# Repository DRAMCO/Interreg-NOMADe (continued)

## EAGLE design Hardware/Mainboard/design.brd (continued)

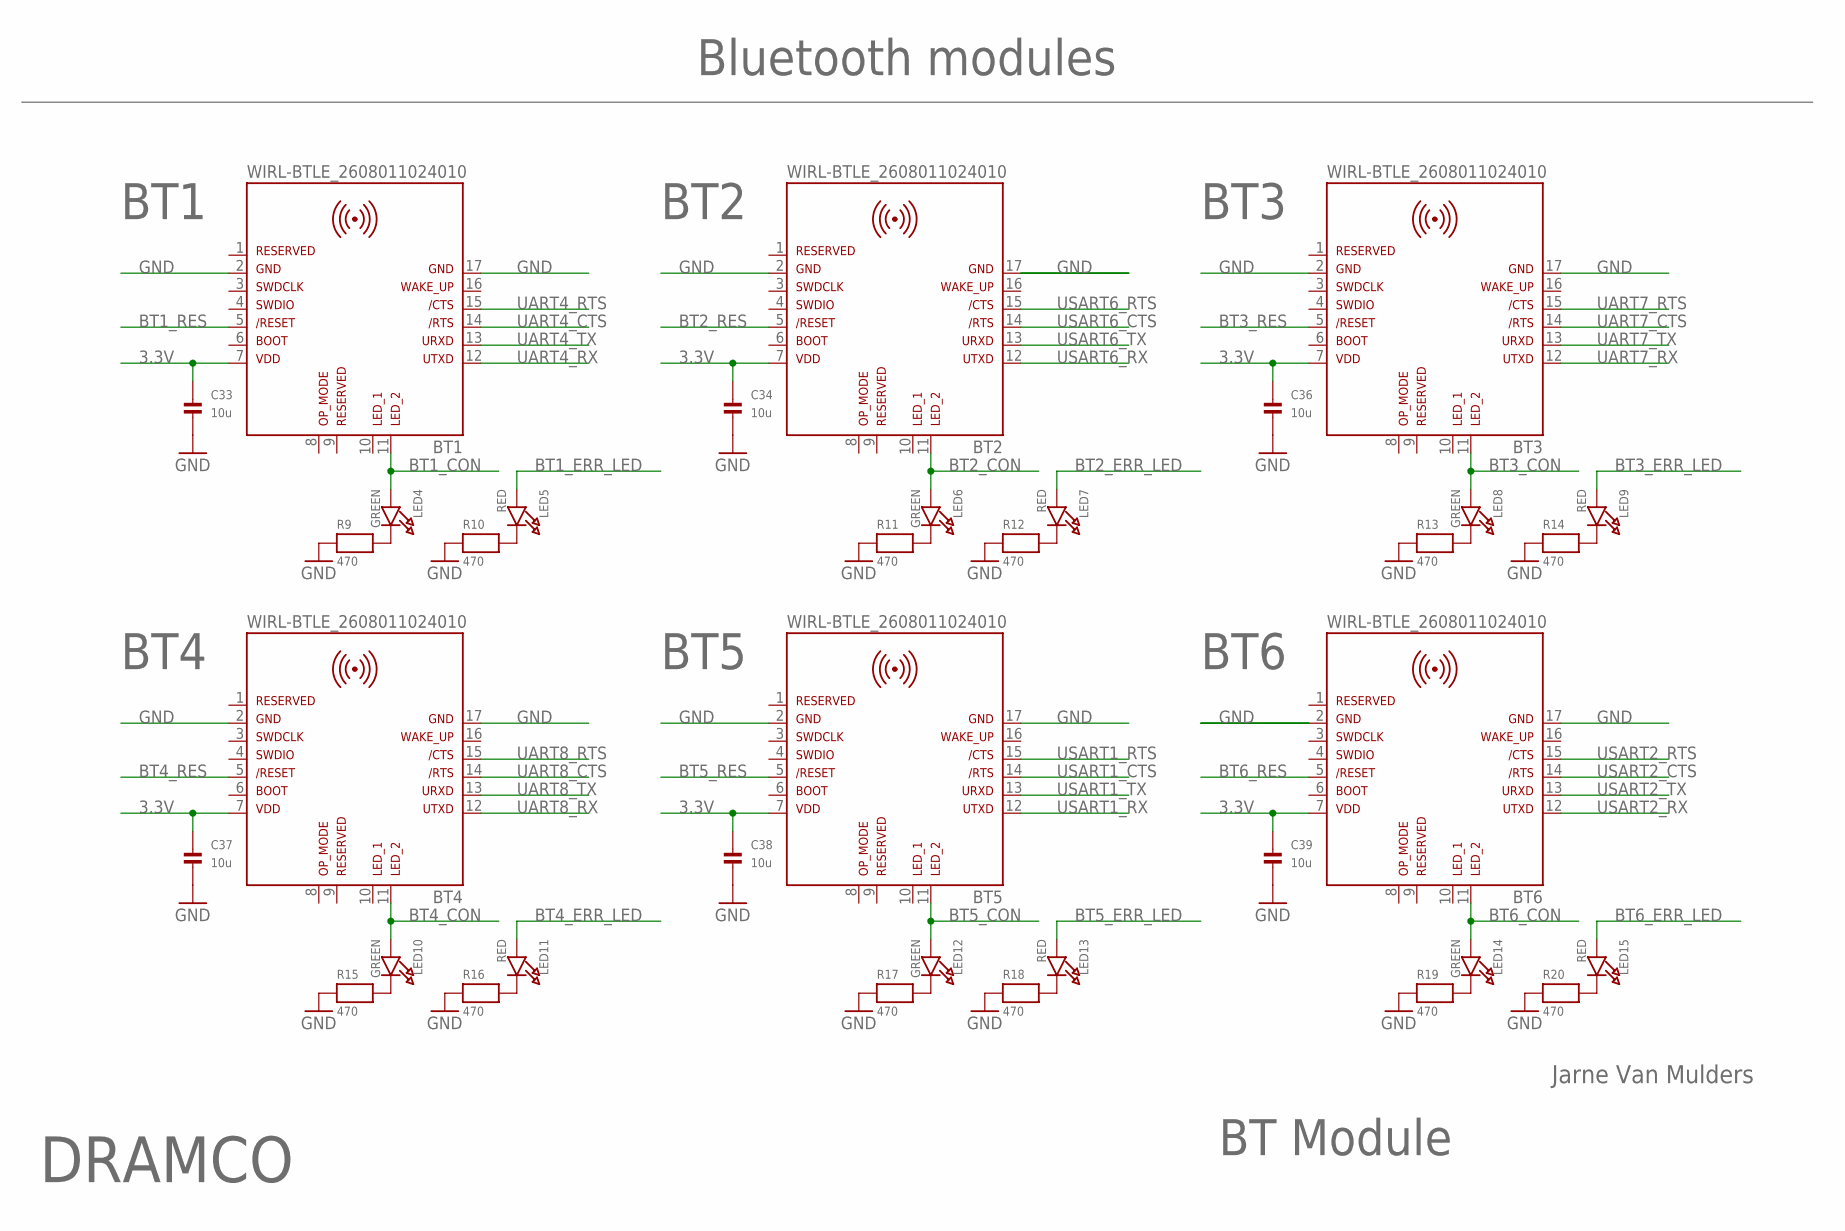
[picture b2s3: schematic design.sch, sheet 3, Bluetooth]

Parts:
BT1, BT2, BT3, BT4, BT5, BT6: WIRL-BTLE_2608011024010
C33, C34, C36, C37, C38, C39: 10u; 0805
LED4, LED6, LED8, LED10, LED12, LED14: GREEN; CHIPLED_0805
LED5, LED7, LED9, LED11, LED13, LED15: RED; CHIPLED_0805
R9, R10, R11, R12, R13, R14, R15, R16, R17, R18, R19, R20: 470; 0603

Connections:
3.3V: BT1.7, BT2.7, BT3.7, BT4.7, BT5.7, BT6.7, C33.1, C34.1, C36.1, C37.1, C38.1, C39.1; also elsewhere on the board
BT1_CON: BT1.11, LED4.A; also elsewhere on the board
BT1_ERR_LED: LED5.A; also elsewhere on the board
BT1_RES: BT1.5; also elsewhere on the board
BT2_CON: BT2.11, LED6.A; also elsewhere on the board
BT2_ERR_LED: LED7.A; also elsewhere on the board
BT2_RES: BT2.5; also elsewhere on the board
BT3_CON: BT3.11, LED8.A; also elsewhere on the board
BT3_ERR_LED: LED9.A; also elsewhere on the board
BT3_RES: BT3.5; also elsewhere on the board
BT4_CON: BT4.11, LED10.A; also elsewhere on the board
BT4_ERR_LED: LED11.A; also elsewhere on the board
BT4_RES: BT4.5; also elsewhere on the board
BT5_CON: BT5.11, LED12.A; also elsewhere on the board
BT5_ERR_LED: LED13.A; also elsewhere on the board
BT5_RES: BT5.5; also elsewhere on the board
BT6_CON: BT6.11, LED14.A; also elsewhere on the board
BT6_ERR_LED: LED15.A; also elsewhere on the board
BT6_RES: BT6.5; also elsewhere on the board
GND: BT1.2, BT1.17, BT2.2, BT2.17, BT3.2, BT3.17, BT4.2, BT4.17, BT5.2, BT5.17, BT6.2, BT6.17, C33.2, C34.2, C36.2, C37.2, C38.2, C39.2, R9.1, R10.1, R11.1, R12.1, R13.1, R14.1, R15.1, R16.1, R17.1, R18.1, R19.1, R20.1; also elsewhere on the board
unnamed: LED4.C, R9.2
unnamed: LED5.C, R10.2
unnamed: LED6.C, R11.2
unnamed: LED7.C, R12.2
unnamed: LED8.C, R13.2
unnamed: LED9.C, R14.2
unnamed: LED10.C, R15.2
unnamed: LED11.C, R16.2
unnamed: LED12.C, R17.2
unnamed: LED13.C, R18.2
unnamed: LED14.C, R19.2
unnamed: LED15.C, R20.2
UART4_CTS: BT1.14; also elsewhere on the board
UART4_RTS: BT1.15; also elsewhere on the board
UART4_RX: BT1.12; also elsewhere on the board
UART4_TX: BT1.13; also elsewhere on the board
UART7_CTS: BT3.14; also elsewhere on the board
UART7_RTS: BT3.15; also elsewhere on the board
UART7_RX: BT3.12; also elsewhere on the board
UART7_TX: BT3.13; also elsewhere on the board
UART8_CTS: BT4.14; also elsewhere on the board
UART8_RTS: BT4.15; also elsewhere on the board
UART8_RX: BT4.12; also elsewhere on the board
UART8_TX: BT4.13; also elsewhere on the board
USART1_CTS: BT5.14; also elsewhere on the board
USART1_RTS: BT5.15; also elsewhere on the board
USART1_RX: BT5.12; also elsewhere on the board
USART1_TX: BT5.13; also elsewhere on the board
USART2_CTS: BT6.14; also elsewhere on the board
USART2_RTS: BT6.15; also elsewhere on the board
USART2_RX: BT6.12; also elsewhere on the board
USART2_TX: BT6.13; also elsewhere on the board
USART6_CTS: BT2.14; also elsewhere on the board
USART6_RTS: BT2.15; also elsewhere on the board
USART6_RX: BT2.12; also elsewhere on the board
USART6_TX: BT2.13; also elsewhere on the board

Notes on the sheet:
BT Module
Jarne Van Mulders
DRAMCO
Bluetooth modules
BT1
BT2
BT3
BT6
BT5
BT4

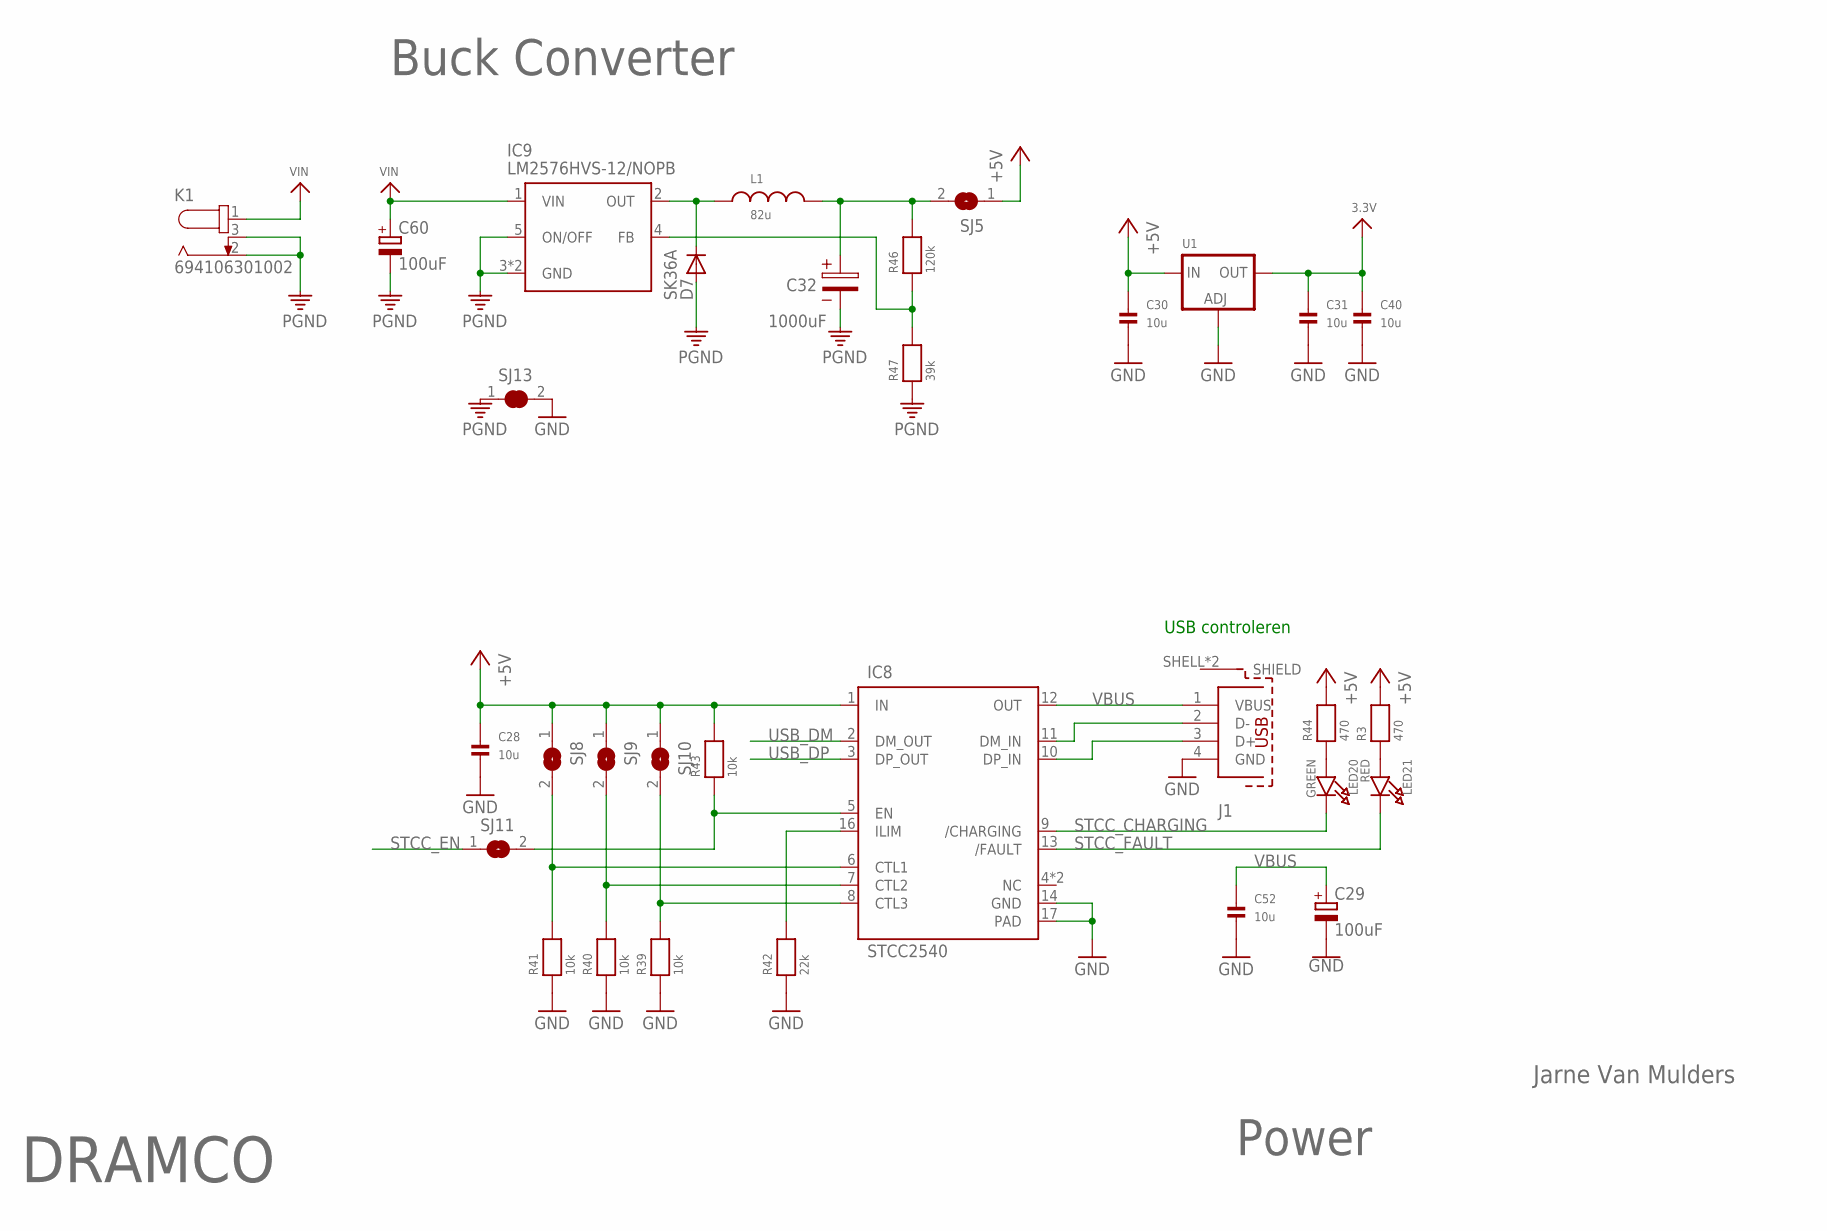
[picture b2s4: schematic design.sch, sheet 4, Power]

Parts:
C28, C30, C31, C40, C52: 10u; 0805
C29, C60: 100uF; E2,5-6
C32: 1000uF; 10X5X0.9(DXAXB)
D7: SK36A; DO214AA
IC8: STCC2540; QFN50P300X300X80-17N
IC9: LM2576HVS-12/NOPB; TO263-5
J1: 614004190021
K1: 694106301002
L1: 82u; WE-PD_1260/1245/1280/1210
LED20: GREEN; CHIPLED_0805
LED21: RED; CHIPLED_0805
R3, R44: 470; 0603
R39, R40, R41, R43: 10k; 0603
R42: 22k; 0603
R46: 120k; 0805
R47: 39k; 0805
SJ5, SJ8, SJ9, SJ10, SJ11: SOLDERJUMPERREFLOW; SOLDERJUMPER_REFLOW
SJ13: SOLDERJUMPER_CLOSED; SOLDERJUMPER_CLOSEDWIRE
U1: LM1117SOT223-REFLOW; SOT223-R

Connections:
3.3V: C31.1, C40.1, U1.2 (OUT); also elsewhere on the board
+5V: C28.1, C30.1, IC8.1 (IN), R3.2, R43.2, R44.2, SJ5.1, SJ8.1, SJ9.1, SJ10.1, U1.3 (IN); also elsewhere on the board
BUCK_OUT: C32.1, L1.2, R46.2, SJ5.2
B_OUT: D7.C, IC9.2 (OUT), L1.1
FB: IC9.4 (FB), R46.1, R47.2
GND: C28.2, C29.-, C30.2, C31.2, C40.2, C52.2, IC8.14 (GND), IC8.17 (PAD), J1.4 (GND), R39.1, R40.1, R41.1, R42.1, SJ13.2, U1.1 (ADJ); also elsewhere on the board
unnamed: LED20.A, R44.1
unnamed: LED21.A, R3.1
unnamed: IC8.16 (ILIM), R42.2
unnamed: IC8.11 (DM_IN), J1.2 (D-)
unnamed: IC8.10 (DP_IN), J1.3 (D+)
unnamed: IC8.8 (CTL3), R39.2, SJ10.2
unnamed: IC8.7 (CTL2), R40.2, SJ9.2
unnamed: IC8.6 (CTL1), R41.2, SJ8.2
unnamed: IC8.5 (EN), R43.1, SJ11.2
PGND: C32.2, C60.-, D7.A, IC9.3 (GND), IC9.5 (ON/OFF), IC9.6 (GND), K1.2, K1.3, R47.1, SJ13.1
STCC_CHARGING: IC8.9 (/CHARGING), LED20.C; also elsewhere on the board
STCC_EN: SJ11.1; also elsewhere on the board
STCC_FAULT: IC8.13 (/FAULT), LED21.C; also elsewhere on the board
USB_DM: IC8.2 (DM_OUT); also elsewhere on the board
USB_DP: IC8.3 (DP_OUT); also elsewhere on the board
VBUS: C29.+, C52.1, IC8.12 (OUT), J1.1 (VBUS)
VIN: C60.+, IC9.1 (VIN), K1.1

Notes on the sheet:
Power
Jarne Van Mulders
DRAMCO
USB controleren
Buck Converter

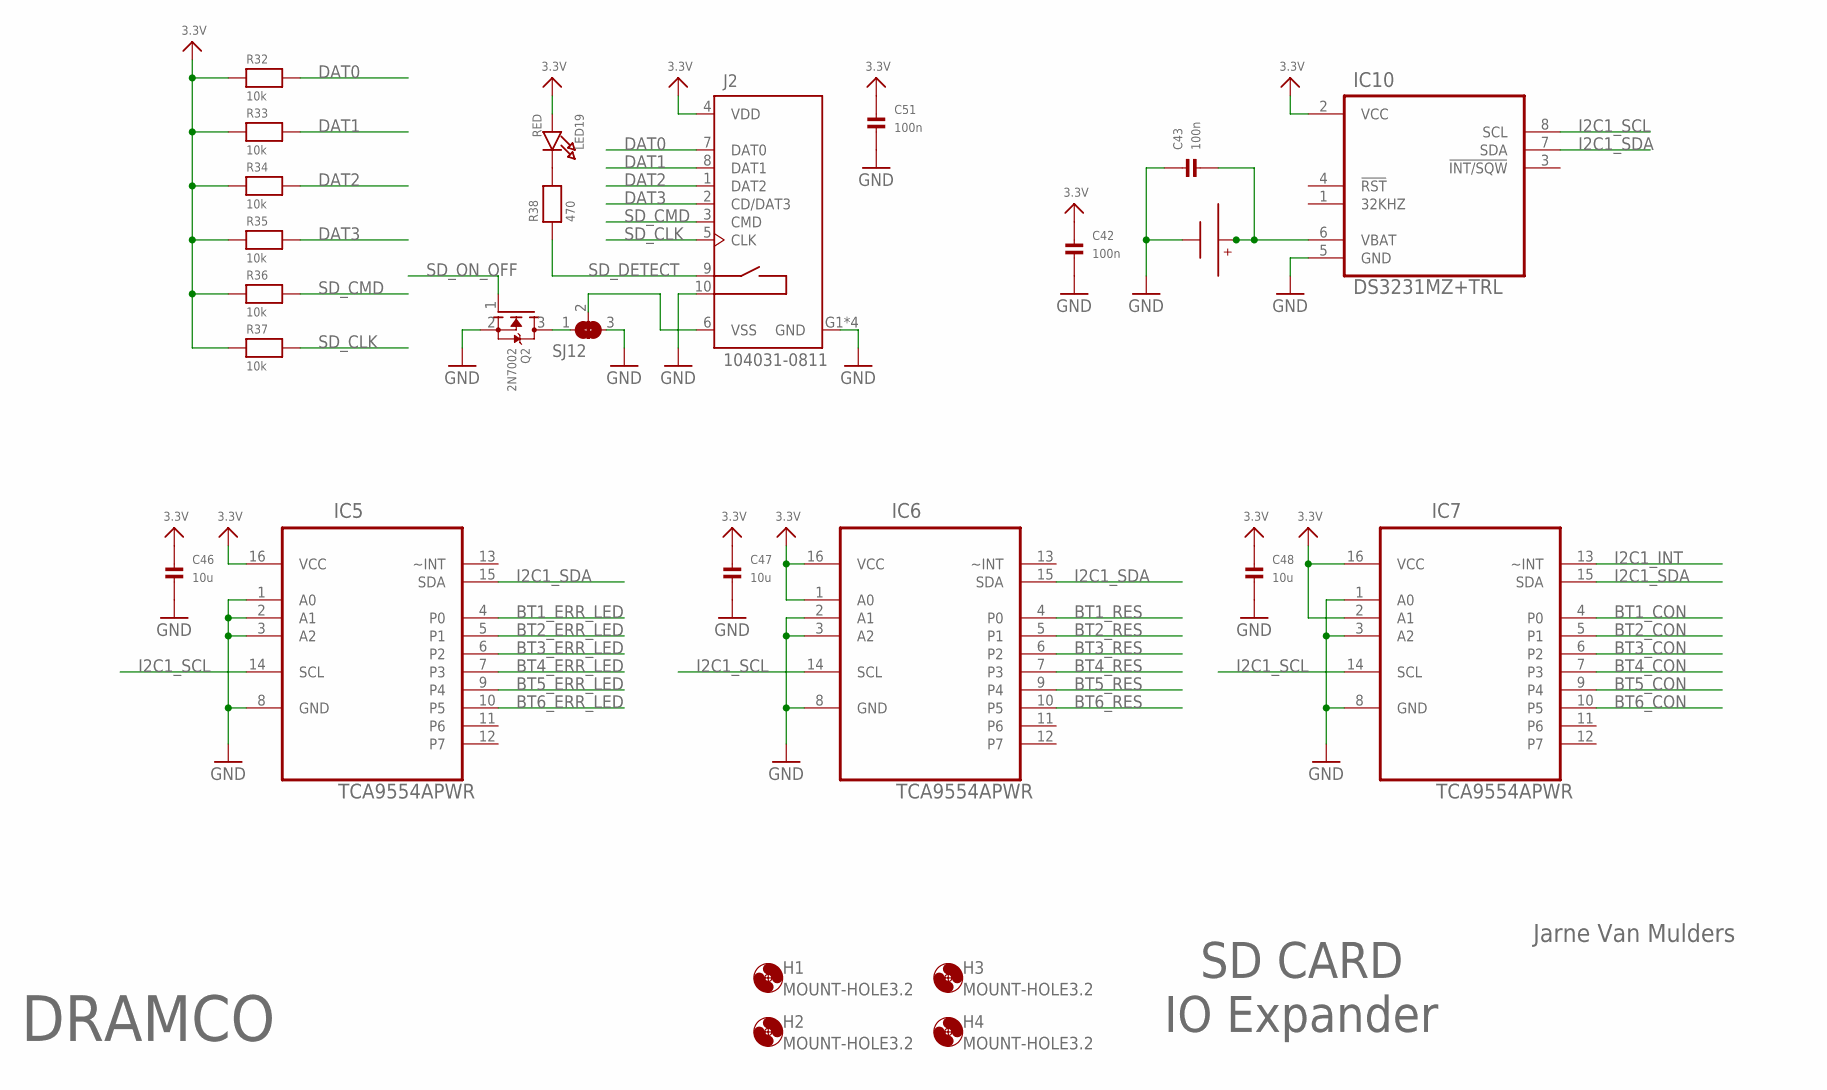
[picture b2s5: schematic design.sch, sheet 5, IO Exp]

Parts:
C42, C43, C51: 100n; 0603
C46, C47, C48: 10u; 0805
H1, H2, H3, H4: MOUNT-HOLE3.2; 3,2
IC5, IC6, IC7: TCA9554APWR; SOP65P640X120-16N
IC10: DS3231MZ+TRL; SOIC127P600X175-8N
J2: 104031-0811; MOLEX_104031-0811
LED19: RED; CHIPLED_0805
Q2: 2N7002; SOT23-WIDE
R32, R33, R34, R35, R36, R37: 10k; 0603
R38: 470; 0603
SJ12: SOLDERJUMPER_2WAY; SOLDERJUMPER_2WAY_OPEN_NOPASTE
U$24: BAT-HLD-001

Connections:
3.3V: C42.1, C46.1, C47.1, C48.1, C51.1, IC5.16 (VCC), IC6.1 (A0), IC6.16 (VCC), IC7.2 (A1), IC7.16 (VCC), IC10.2 (VCC), J2.4 (VDD), LED19.A, R32.1, R33.1, R34.1, R35.1, R36.1, R37.1; also elsewhere on the board
BT1_CON: IC7.4 (P0); also elsewhere on the board
BT1_ERR_LED: IC5.4 (P0); also elsewhere on the board
BT1_RES: IC6.4 (P0); also elsewhere on the board
BT2_CON: IC7.5 (P1); also elsewhere on the board
BT2_ERR_LED: IC5.5 (P1); also elsewhere on the board
BT2_RES: IC6.5 (P1); also elsewhere on the board
BT3_CON: IC7.6 (P2); also elsewhere on the board
BT3_ERR_LED: IC5.6 (P2); also elsewhere on the board
BT3_RES: IC6.6 (P2); also elsewhere on the board
BT4_CON: IC7.7 (P3); also elsewhere on the board
BT4_ERR_LED: IC5.7 (P3); also elsewhere on the board
BT4_RES: IC6.7 (P3); also elsewhere on the board
BT5_CON: IC7.9 (P4); also elsewhere on the board
BT5_ERR_LED: IC5.9 (P4); also elsewhere on the board
BT5_RES: IC6.9 (P4); also elsewhere on the board
BT6_CON: IC7.10 (P5); also elsewhere on the board
BT6_ERR_LED: IC5.10 (P5); also elsewhere on the board
BT6_RES: IC6.10 (P5); also elsewhere on the board
DAT0: J2.7 (DAT0), R32.2; also elsewhere on the board
DAT1: J2.8 (DAT1), R33.2; also elsewhere on the board
DAT2: J2.1 (DAT2), R34.2; also elsewhere on the board
DAT3: J2.2 (CD/DAT3), R35.2; also elsewhere on the board
GND: C42.2, C43.1, C46.2, C47.2, C48.2, C51.2, IC5.1 (A0), IC5.2 (A1), IC5.3 (A2), IC5.8 (GND), IC6.2 (A1), IC6.3 (A2), IC6.8 (GND), IC7.1 (A0), IC7.3 (A2), IC7.8 (GND), IC10.5 (GND), J2.10 (CARD_DET2), J2.G1 (GND), J2.G2 (GND), J2.G3 (GND), J2.G4 (GND), Q2.2 (S), SJ12.3, U$24.-; also elsewhere on the board
I2C1_INT: IC7.13 (~INT); also elsewhere on the board
I2C1_SCL: IC5.14 (SCL), IC6.14 (SCL), IC7.14 (SCL), IC10.8 (SCL); also elsewhere on the board
I2C1_SDA: IC5.15 (SDA), IC6.15 (SDA), IC7.15 (SDA), IC10.7 (SDA); also elsewhere on the board
unnamed: J2.6 (VSS), SJ12.2
unnamed: Q2.3 (D), SJ12.1
unnamed: LED19.C, R38.2
unnamed: C43.2, IC10.6 (VBAT), U$24.+@1 (+), U$24.+@2 (+)
SD_CLK: J2.5 (CLK), R37.2; also elsewhere on the board
SD_CMD: J2.3 (CMD), R36.2; also elsewhere on the board
SD_DETECT: J2.9 (CARD_DET1), R38.1; also elsewhere on the board
SD_ON_OFF: Q2.1 (G); also elsewhere on the board

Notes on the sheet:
IO Expander
Jarne Van Mulders
DRAMCO
SD CARD

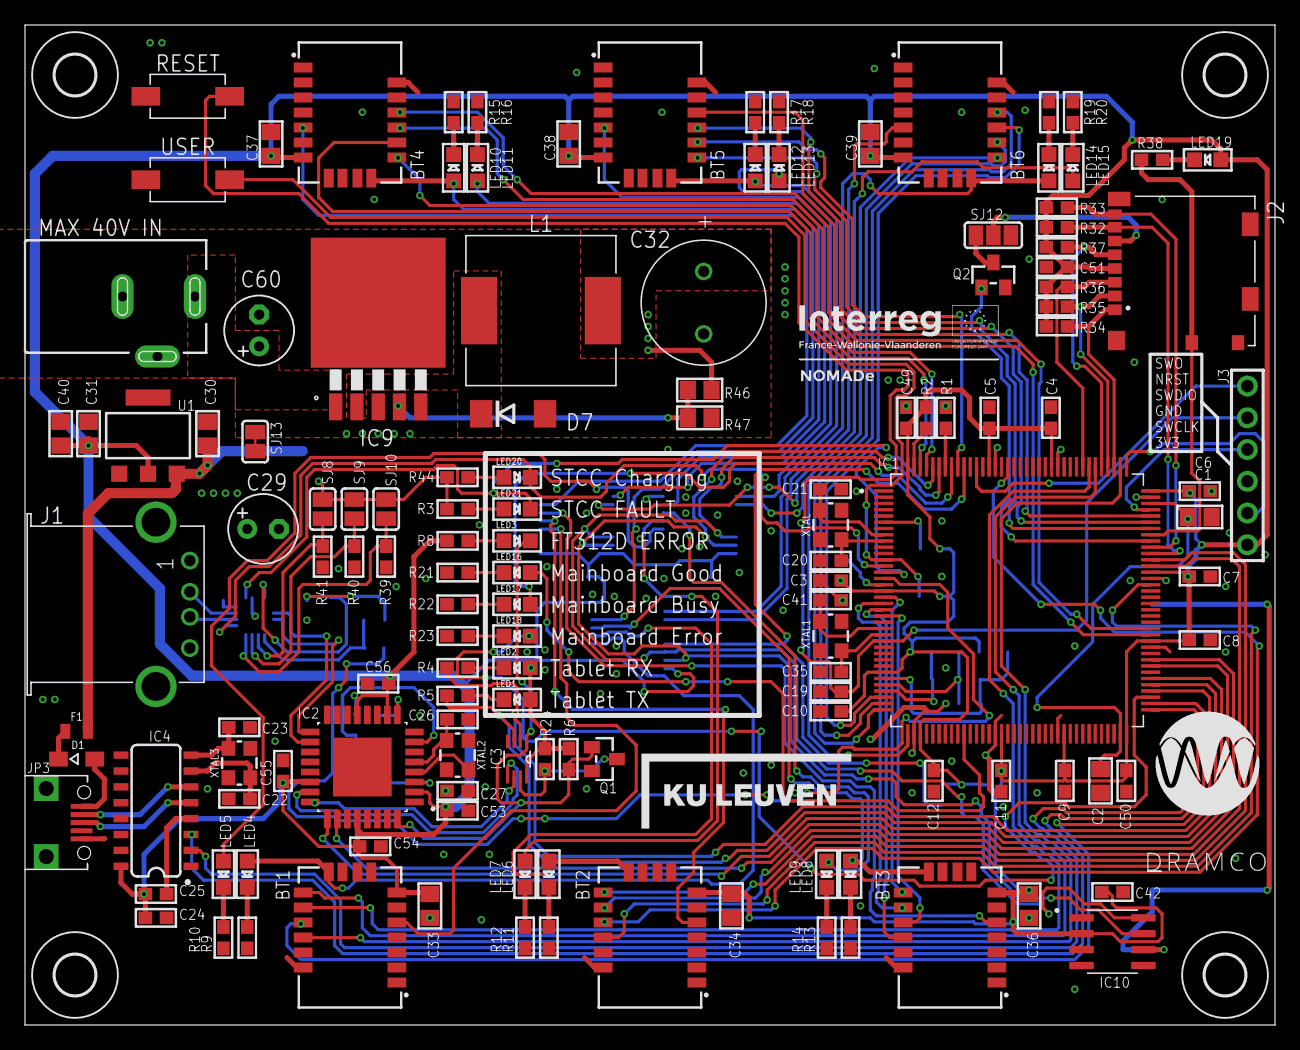
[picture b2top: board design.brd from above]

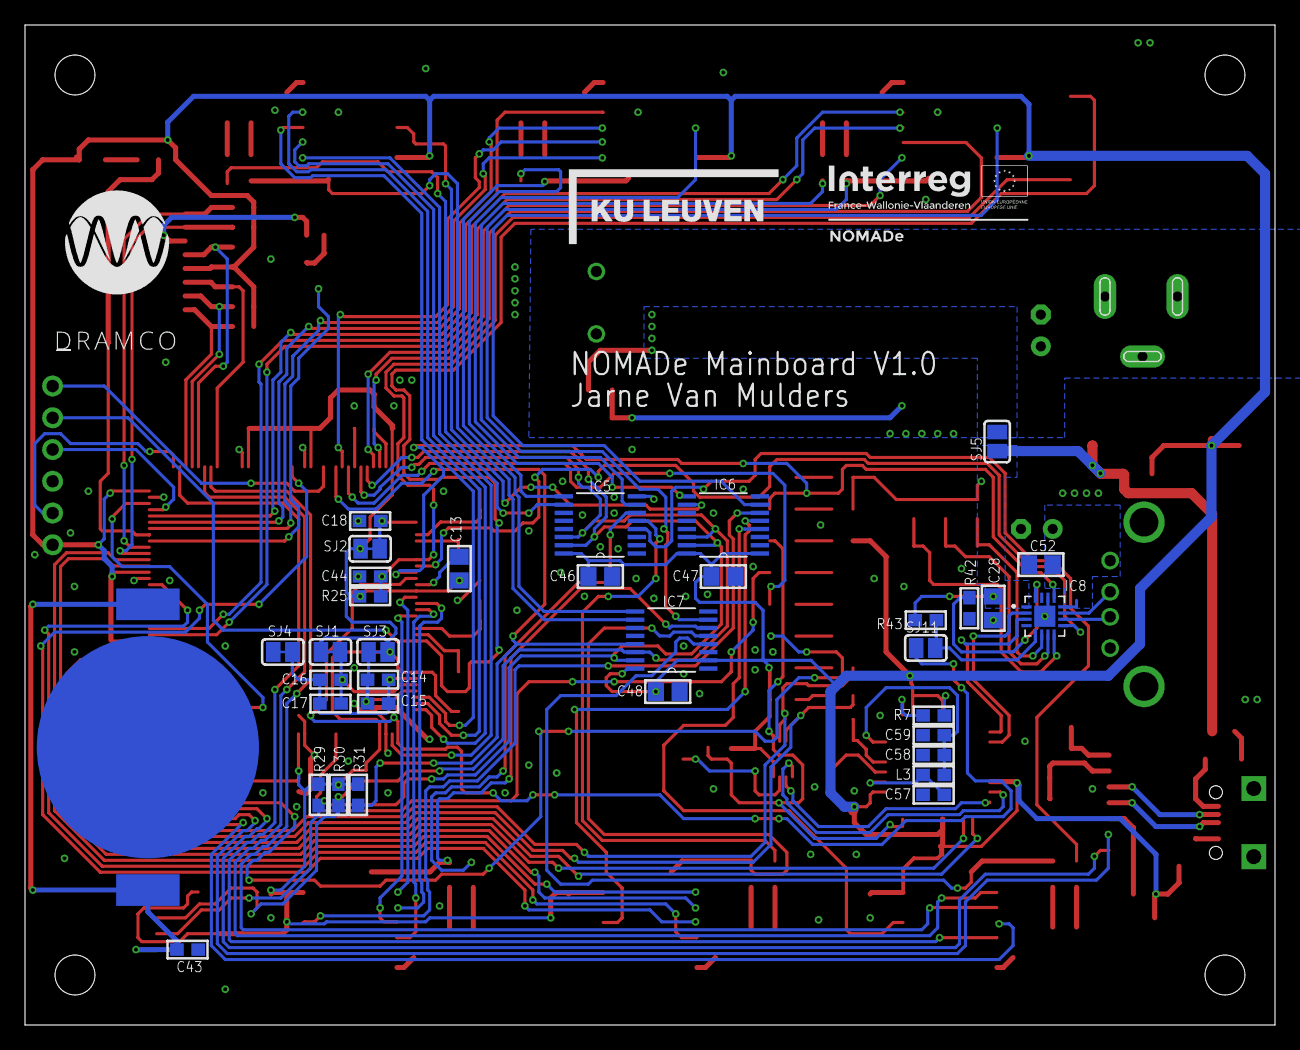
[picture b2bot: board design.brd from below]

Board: 2 copper layers, 99.9 x 79.9 mm, 174 parts (35 on the bottom side), 139 nets.

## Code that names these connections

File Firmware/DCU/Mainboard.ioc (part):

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Mcu.Name=STM32H743ZITx
Mcu.Package=LQFP144
Mcu.UserName=STM32H743ZITx
PA0.Mode=CTS_RTS
PA0.Signal=USART2_CTS
PA1.Mode=CTS_RTS
PA1.Signal=USART2_RTS
PA10.Mode=Asynchronous
PA10.Signal=USART1_RX
PA11.Mode=CTS_RTS
PA11.Signal=USART1_CTS
PA12.Mode=CTS_RTS
PA12.Signal=USART1_RTS
PA15\ (JTDI).Mode=CTS_RTS
PA15\ (JTDI).Signal=UART4_RTS
PA2.Mode=Asynchronous
PA2.Signal=USART2_TX
PA3.Mode=Asynchronous
PA3.Signal=USART2_RX
PA8.GPIOParameters=GPIO_Label
PA8.GPIO_Label=SD_ON_OFF
PA8.Signal=GPIO_Output
PA9.GPIOParameters=GPIO_Label
PA9.GPIO_Label=SD_DETECT
PA9.Signal=GPIO_Input
PB0.GPIOParameters=GPIO_Label
PB0.GPIO_Label=LED_GOOD
PB0.Signal=GPIO_Output
PB12.Mode=Asynchronous
PB12.Signal=UART5_RX
PB13.Mode=Asynchronous
PB13.Signal=UART5_TX
PB14.GPIOParameters=GPIO_Label
PB14.GPIO_Label=LED_ERROR
PB14.Signal=GPIO_Output
PB15.Mode=CTS_RTS
PB15.Signal=UART4_CTS
PB5.GPIOParameters=GPIO_Label
PB5.GPIO_Label=I2C1_INT
PB5.Signal=GPXTI5
PB6.Mode=Asynchronous
PB6.Signal=USART1_TX
PB7.GPIOParameters=GPIO_Label
PB7.GPIO_Label=LED_BUSY
PB7.Signal=GPIO_Output
PB8.Mode=I2C
PB8.Signal=I2C1_SCL
PB9.Mode=I2C
PB9.Signal=I2C1_SDA
PC10.Mode=SD_4_bits_Wide_bus
PC10.Signal=SDMMC1_D2
PC11.Mode=SD_4_bits_Wide_bus
PC11.Signal=SDMMC1_D3
PC12.Mode=SD_4_bits_Wide_bus
PC12.Signal=SDMMC1_CK
PC6.Mode=Asynchronous
PC6.Signal=USART6_TX
PC7.Mode=Asynchronous
PC7.Signal=USART6_RX
PC8.Mode=SD_4_bits_Wide_bus
PC8.Signal=SDMMC1_D0
PC9.Mode=SD_4_bits_Wide_bus
PC9.Signal=SDMMC1_D1
PD0.Mode=Asynchronous
PD0.Signal=UART4_RX
PD1.Mode=Asynchronous
PD1.Signal=UART4_TX
PD11.Mode=CTS_RTS
PD11.Signal=USART3_CTS
PD12.Mode=CTS_RTS
PD12.Signal=USART3_RTS
PD14.Mode=CTS_RTS
PD14.Signal=UART8_CTS
PD15.Mode=CTS_RTS
PD15.Signal=UART8_RTS
PD2.Mode=SD_4_bits_Wide_bus
PD2.Signal=SDMMC1_CMD
PD8.Mode=Asynchronous
PD8.Signal=USART3_TX
PD9.Mode=Asynchronous
PD9.Signal=USART3_RX
PE0.Mode=Asynchronous
PE0.Signal=UART8_RX
PE1.Mode=Asynchronous
PE1.Signal=UART8_TX
PF2.GPIOParameters=GPIO_Label
PF2.GPIO_Label=USER_BUTTON
PF2.Signal=GPXTI2
PF3.GPIOParameters=GPIO_Label
PF3.GPIO_Label=STCC_CHARGING
PF3.Signal=GPIO_Input
PF4.GPIOParameters=GPIO_Label
PF4.GPIO_Label=STCC_FAULT
PF4.Signal=GPIO_Input
PF5.GPIOParameters=GPIO_Label
PF5.GPIO_Label=STCC_EN
PF5.Signal=GPIO_Output
PF6.Mode=Asynchronous
PF6.Signal=UART7_RX
PF7.Mode=Asynchronous
PF7.Signal=UART7_TX
PF8.Mode=CTS_RTS
PF8.Signal=UART7_RTS
PF9.Mode=CTS_RTS
PF9.Signal=UART7_CTS
PG13.Mode=CTS_RTS
PG13.Signal=USART6_CTS
PG8.Mode=CTS_RTS
PG8.Signal=USART6_RTS
RCC.SYSCLKFreq_VALUE=64000000
board=custom

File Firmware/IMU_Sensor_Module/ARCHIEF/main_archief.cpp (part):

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// ===                    Define MCU pins                       ===
// ================================================================

#define MPU_INT             2
#define BUTTON_INT          3
#define CHECK_BAT           4
#define BT_STATUS           5     
#define BT_CTS              6
#define BT_RTS              7
#define IND_LED             13
//#define WAKE_UP_PIN


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    #endif

    mpu.initialize();
    pinMode(MPU_INT, INPUT);

    //  Verify connection
    #ifdef DEBUG 
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        #ifdef DEBUG
          // enable Arduino interrupt detection
          Serial.print(F("Enabling interrupt detection (Arduino external interrupt "));
          Serial.print(digitalPinToInterrupt(MPU_INT));
          Serial.println(F(")..."));
        #endif

        //attachInterrupt(digitalPinToInterrupt(MPU_INT), dmpDataReady, RISING);
        mpuIntStatus = mpu.getIntStatus();

        #ifdef DEBUG
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    #endif

      //  Configure IN- and OUTPUTS
    pinMode(IND_LED, OUTPUT);
    pinMode(BT_CTS, OUTPUT);
    pinMode(BT_RTS, OUTPUT);
    pinMode(CHECK_BAT, OUTPUT);
    pinMode(BT_STATUS, INPUT);
    //pinMode(WAKE_UP_PIN, OUTPUT);

    digitalWrite(IND_LED, LOW);
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void loop() {
    // Allow wake up pin to trigger interrupt on low.
    //attachInterrupt(0, wakeUp, LOW);
  attachInterrupt(digitalPinToInterrupt(MPU_INT), dmpDataReady, RISING);
  Serial.flush();
  
    // Enter power down state with ADC and BOD module disabled.
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// ===                    Define MCU pins                       ===
// ================================================================

#define MPU_INT             2
#define BUTTON_INT          3
#define CHECK_BAT           4
#define BT_STATUS           5     
#define BT_CTS              6
#define BT_RTS              7
#define IND_LED             13
//#define WAKE_UP_PIN


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    // initialize device
    Serial.println(F("Initializing I2C devices..."));
    mpu.initialize();
    pinMode(MPU_INT, INPUT);

    //  Verify connection
    #ifdef DEBUG 
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
        // enable Arduino interrupt detection
        Serial.print(F("Enabling interrupt detection (Arduino external interrupt "));
        Serial.print(digitalPinToInterrupt(MPU_INT));
        Serial.println(F(")..."));
        attachInterrupt(digitalPinToInterrupt(MPU_INT), dmpDataReady, RISING);
        mpuIntStatus = mpu.getIntStatus();

        // set our DMP Ready flag so the main loop() function knows it's okay to use it
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    }

    // configure LED for output
    pinMode(IND_LED, OUTPUT);
}


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
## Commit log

2020-02-27 Initial commit
    Creation of the hardware and firmware for the mainboard and IMU sensor module
2020-02-27 Initial commit
    Creation of the hardware for the mainboard and IMU sensor module
2020-02-27 Schematics
    Add the schematics in pdf format
2020-02-28 Sampling frequency settable
    Sampling freq 25
    BT baudrate 115200
    Current flow during normal operation 5.7mA
2020-04-03 Firmware + creation script + hardware sensor update
    Firmware update for IMU module + creation of python script for visualisation of the sensor data + minor adjustments to the circuit board of the IMU sensor module
2020-04-03 Add python scripts
    Initial commit python scripts
2020-04-03 Update minor adjustments
2020-05-25 Revision DCU
    DCU (Data Capture Unit) = mainboard
    - Save IMU data on SD card
    - Make connection with IMU module
2020-05-25 Update IMU Sensor Module Firmware
    Code transition to state machine
2020-06-09 Bidirectional bluetooth communication
    - Start connected modules synchronusly
    - Bidirectional communication
    - IMU calibration can be determined from the mainboard
2020-07-06 Additional commands bidirection communication
    Commands added like:
    - get battery voltage (tested)
    - start/stop measurements (tested)
    - change sampling frequency (not tested)
    - got to sleep (tested)
2020-08-13 Implementing Ringbuffers
    - Implementation Ringbuffer for all UART streams
    - Starded on simple MENU for management with COM port
    - Clean code (remove ble_lib, changed name ble to proteusII_driver, ...)
2020-08-20 Add USB control
    Make software ready for the first measurements
    Via USB interface controllable:
    - connect/disconnect
    - start/stop measurements
    - calibration/synchronisation IMU modules
    - create new file SD card
2020-08-28 Cleaning the code
    Add and remove comment lines
2020-08-28 Update README
    Add the drawings to the repository
2020-08-28 Added citation info
2020-10-15 Final software update
    - Python script added with example
    - Software updated (last update before sending to university partners)
2020-10-26 Python script minor adjustments
    - Problem in the script prevented the creation of the YPR graph
    - Manual added
2020-11-08 Update IMU Module Code
    Cleaning IMU Module code
    IMU Module SW V3.0
    Preparing code for new improvements
2020-11-12 Update Firmware DCU + IMU module
    IMU Module SW V3.1
    DCU SW3.0
    New data echange format
    - only quaternions (was already implemented)
    - quaternions + gyroscope + accelerometer (new data format)
2020-11-26 Update software IMU Module & DCU
    IMU Sensor Module SW V3.2
    DCU SW V3.1
    - Data format adjustable
    - Get SW version IMU Sensor Module
    - Start measurement without synchronisation
2020-11-30 Update Manual and added Python script
    - New python script enables the comparison between the orientations of two sensor modules.
    - Manual V2.0 is now available
2021-03-01 Minor adjustments
    Possibility to adjust the baudrate between MCU and Proteus-II BLE modem
    The adjustment applies to the IMU Sensor module
2021-04-16 Add logo
2021-04-16 Logo update
